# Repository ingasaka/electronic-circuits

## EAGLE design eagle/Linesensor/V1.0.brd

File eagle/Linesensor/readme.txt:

Linesensor V1.0 by ASAKA 2015

Popis:

Maximalne pouzitelne napajacie napatie +5V.

PINY:

1 - OUT 2 - from IC2 
2 - OUT 1 - from IC1
3 - OUT 4 - from IC4
4 - OUT 3 - from IC3
5 - GND
6 - V+(max.+5V)

Video nahlad: https://www.youtube.com/watch?v=R8Qme-guCv8

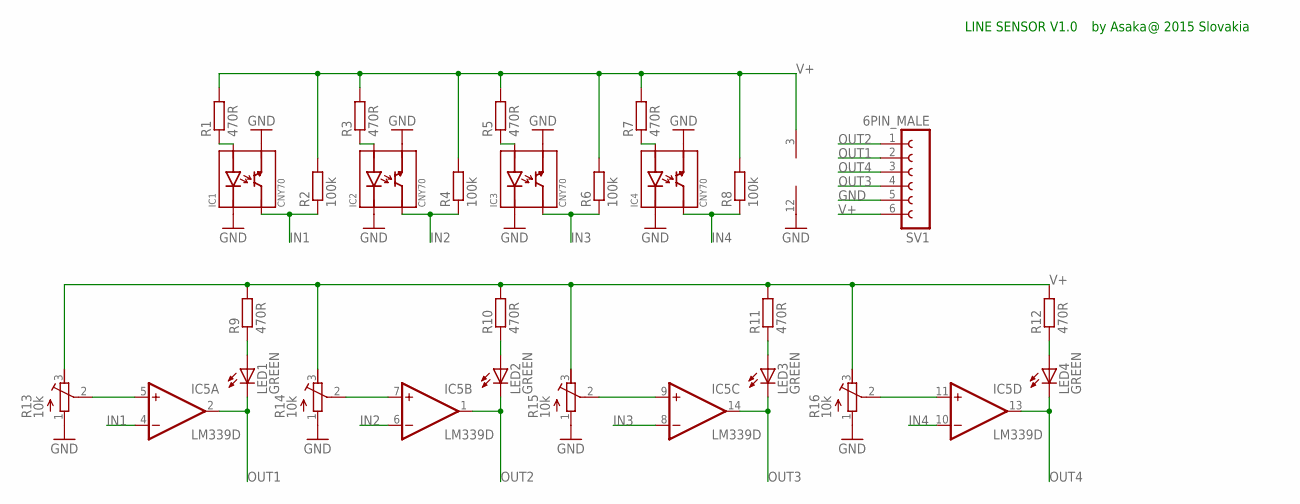
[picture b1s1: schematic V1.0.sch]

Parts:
IC1, IC2, IC3, IC4: CNY70
IC5: LM339D; SO14
LED1, LED2, LED3, LED4: GREEN; CHIP-LED0805
R1, R3, R5, R7, R9, R10, R11, R12: 470R; M0805
R2, R4, R6, R8: 100k; M0805
R13, R14, R15, R16: 10k; RTRIM3202
SV1: 6PIN_MALE; FE06

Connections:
GND: IC1.DE, IC1.EK, IC2.DE, IC2.EK, IC3.DE, IC3.EK, IC4.DE, IC4.EK, IC5.12 (GND), R13.1 (E), R14.1 (E), R15.1 (E), R16.1 (E), SV1.5
IN1: IC1.DC, IC5.4 (-IN), R2.1
IN2: IC2.DC, IC5.6 (-IN), R4.1
IN3: IC3.DC, IC5.8 (-IN), R6.1
IN4: IC4.DC, IC5.10 (-IN), R8.1
unnamed: IC5.5 (+IN), R13.2 (S)
unnamed: IC5.7 (+IN), R14.2 (S)
unnamed: IC5.9 (+IN), R15.2 (S)
unnamed: IC5.11 (+IN), R16.2 (S)
unnamed: LED1.A, R9.1
unnamed: LED2.A, R10.1
unnamed: LED3.A, R11.1
unnamed: LED4.A, R12.1
unnamed: IC1.EA, R1.1
unnamed: IC2.EA, R3.1
unnamed: IC3.EA, R5.1
unnamed: IC4.EA, R7.1
OUT1: IC5.2 (OUT), LED1.C, SV1.2
OUT2: IC5.1 (OUT), LED2.C, SV1.1
OUT3: IC5.14 (OUT), LED3.C, SV1.4
OUT4: IC5.13 (OUT), LED4.C, SV1.3
V+: IC5.3 (V+), R1.2, R2.2, R3.2, R4.2, R5.2, R6.2, R7.2, R8.2, R9.2, R10.2, R11.2, R12.2, R13.3 (A), R14.3 (A), R15.3 (A), R16.3 (A), SV1.6

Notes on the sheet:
LINE SENSOR V1.0
by Asaka
@ 2015 Slovakia

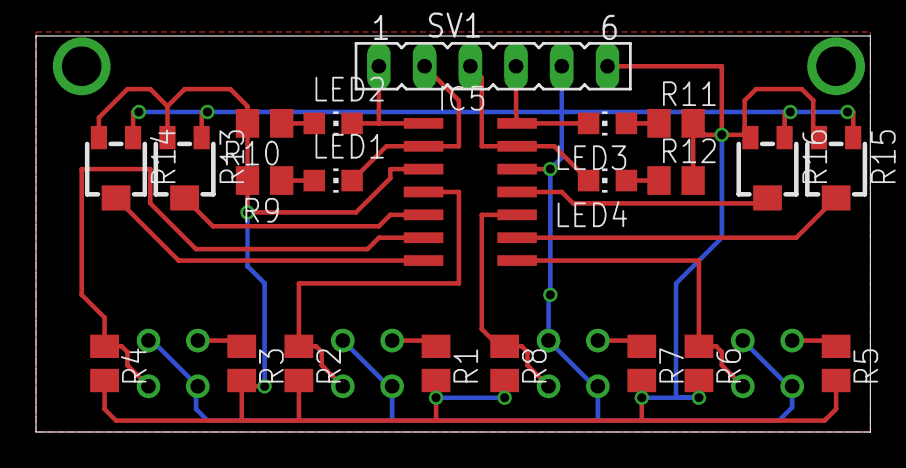
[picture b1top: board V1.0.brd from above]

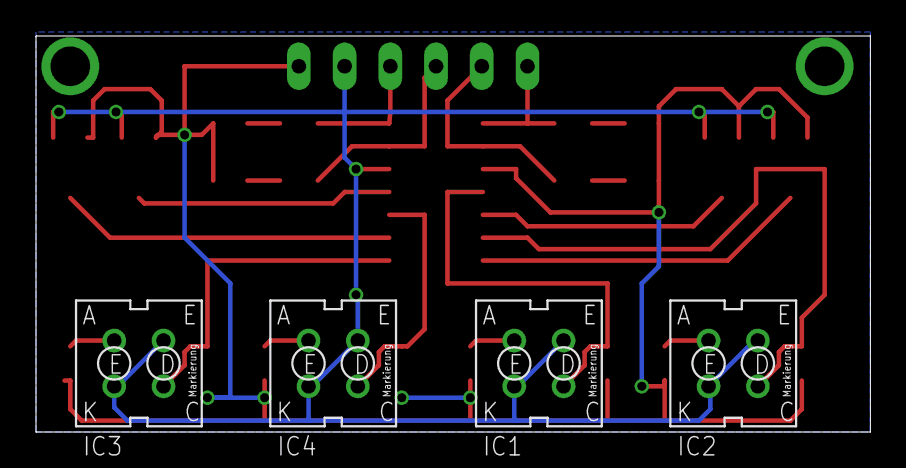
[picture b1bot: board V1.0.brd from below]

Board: 2 copper layers, 46.4 x 22.0 mm, 26 parts (4 on the bottom side), 22 nets.

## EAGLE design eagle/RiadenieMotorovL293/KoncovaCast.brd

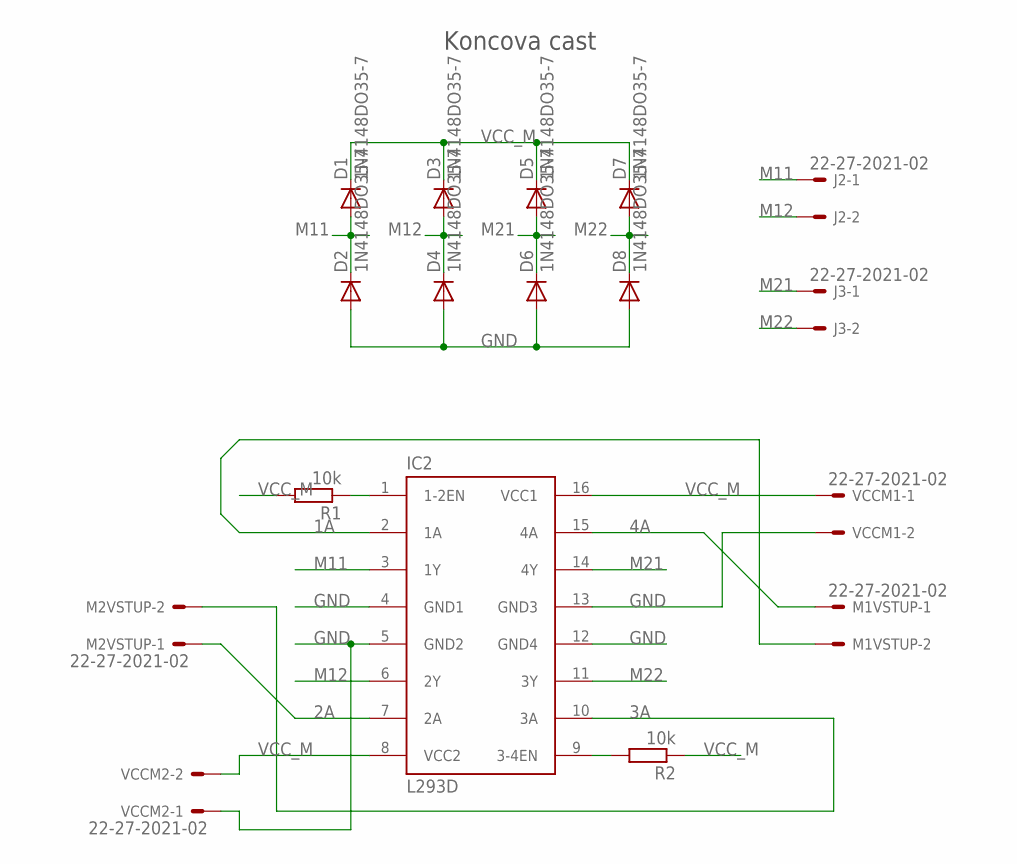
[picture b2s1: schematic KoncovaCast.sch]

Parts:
D1, D2, D3, D4, D5, D6, D7, D8: 1N4148DO35-7; DO35-7
IC2: L293D; DIL16
J2, J3: 22-27-2021-02; 6410-02
M1VSTUP, M2VSTUP: 22-27-2021-02; 6410-02
R1, R2: 10k; 0204V
VCCM1, VCCM2: 22-27-2021-02; 6410-02

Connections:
1A: IC2.2 (1A), M1VSTUP.2
2A: IC2.7 (2A), M2VSTUP.1
3A: IC2.10 (3A), M2VSTUP.2
4A: IC2.15 (4A), M1VSTUP.1
GND: D2.A, D4.A, D6.A, D8.A, IC2.4 (GND1), IC2.5 (GND2), IC2.12 (GND4), IC2.13 (GND3), VCCM1.2, VCCM2.1
M11: D1.A, D2.C, IC2.3 (1Y), J2.1
M12: D3.A, D4.C, IC2.6 (2Y), J2.2
M21: D5.A, D6.C, IC2.14 (4Y), J3.1
M22: D7.A, D8.C, IC2.11 (3Y), J3.2
unnamed: IC2.1 (1-2EN), R1.1
unnamed: IC2.9 (3-4EN), R2.2
VCC_M: D1.C, D3.C, D5.C, D7.C, IC2.8 (VCC2), IC2.16 (VCC1), R1.2, R2.1, VCCM1.1, VCCM2.2

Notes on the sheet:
Koncova cast

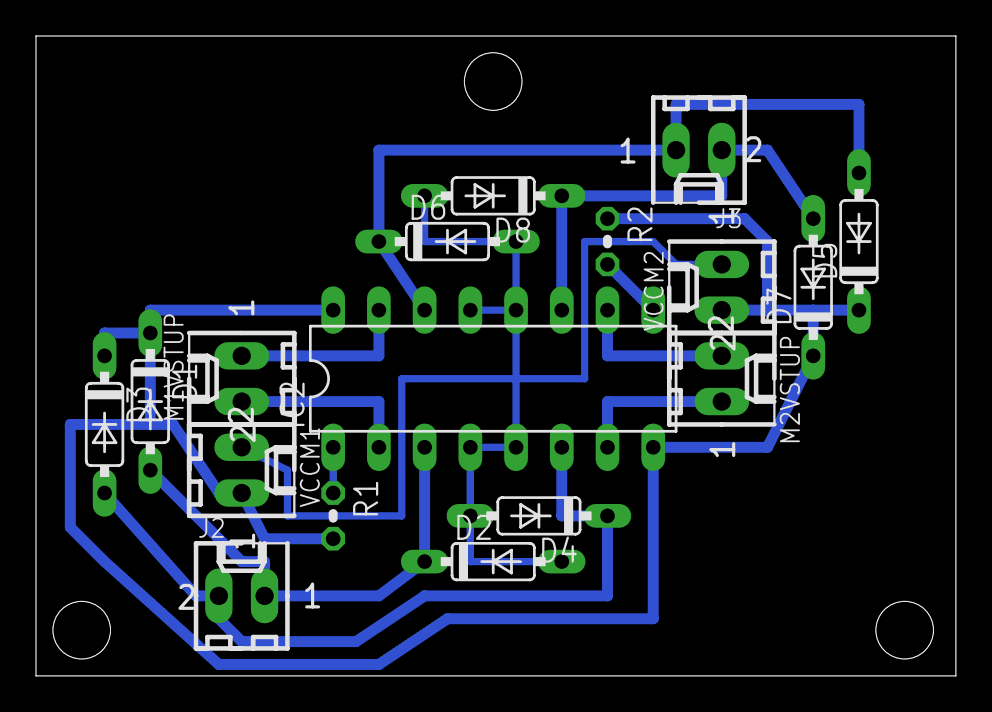
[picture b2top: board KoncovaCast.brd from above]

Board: 2 copper layers, 51.1 x 35.5 mm, 17 parts (0 on the bottom side), 12 nets.

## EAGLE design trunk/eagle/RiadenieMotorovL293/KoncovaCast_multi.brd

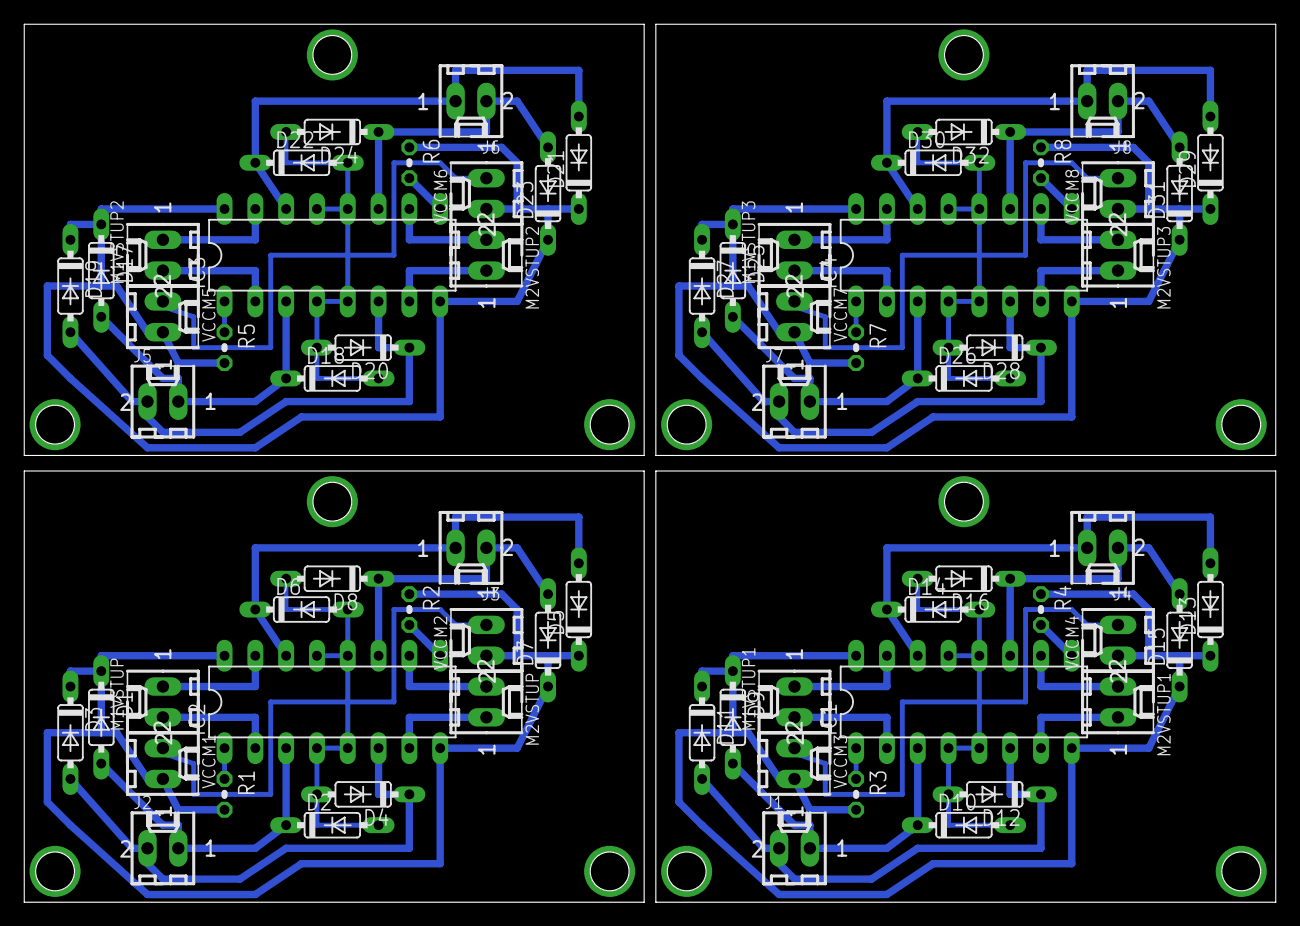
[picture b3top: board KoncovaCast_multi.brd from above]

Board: 2 copper layers, 103.2 x 72.4 mm, 68 parts (0 on the bottom side), 48 nets.

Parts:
D1, D2, D3, D4, D5, D6, D7, D8, D9, D10, D11, D12, D13, D14, D15, D16, D17, D18, D19, D20, D21, D22, D23, D24, D25, D26, D27, D28, D29, D30, D31, D32: 1N4148DO35-7; DO35-7
IC1, IC2, IC3, IC4: L293D; DIL16
J1, J2, J3, J4, J5, J6, J7, J8: 22-27-2021-02; 6410-02
M1VSTUP, M1VSTUP1, M1VSTUP2, M1VSTUP3, M2VSTUP, M2VSTUP1, M2VSTUP2, M2VSTUP3: 22-27-2021-02; 6410-02
R1, R2, R3, R4, R5, R6, R7, R8: 10k; 0204V
VCCM1, VCCM2, VCCM3, VCCM4, VCCM5, VCCM6, VCCM7, VCCM8: 22-27-2021-02; 6410-02

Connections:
1A: IC2.2, M1VSTUP.2
1A1: IC1.2, M1VSTUP1.2
1A2: IC3.2, M1VSTUP2.2
1A3: IC4.2, M1VSTUP3.2
2A: IC2.7, M2VSTUP.1
2A1: IC1.7, M2VSTUP1.1
2A2: IC3.7, M2VSTUP2.1
2A3: IC4.7, M2VSTUP3.1
3A: IC2.10, M2VSTUP.2
3A1: IC1.10, M2VSTUP1.2
3A2: IC3.10, M2VSTUP2.2
3A3: IC4.10, M2VSTUP3.2
4A: IC2.15, M1VSTUP.1
4A1: IC1.15, M1VSTUP1.1
4A2: IC3.15, M1VSTUP2.1
4A3: IC4.15, M1VSTUP3.1
GND: D2.A, D4.A, D6.A, D8.A, IC2.4, IC2.5, IC2.12, IC2.13, VCCM1.2, VCCM2.1
GND1: D10.A, D12.A, D14.A, D16.A, IC1.4, IC1.5, IC1.12, IC1.13, VCCM3.2, VCCM4.1
GND2: D18.A, D20.A, D22.A, D24.A, IC3.4, IC3.5, IC3.12, IC3.13, VCCM5.2, VCCM6.1
GND3: D26.A, D28.A, D30.A, D32.A, IC4.4, IC4.5, IC4.12, IC4.13, VCCM7.2, VCCM8.1
M1: D9.A, D10.C, IC1.3, J1.1
M2: D11.A, D12.C, IC1.6, J1.2
M3: D15.A, D16.C, IC1.11, J4.2
M4: D13.A, D14.C, IC1.14, J4.1
M5: D17.A, D18.C, IC3.3, J5.1
M6: D19.A, D20.C, IC3.6, J5.2
M7: D23.A, D24.C, IC3.11, J6.2
M8: D21.A, D22.C, IC3.14, J6.1
M9: D25.A, D26.C, IC4.3, J7.1
M10: D27.A, D28.C, IC4.6, J7.2
M11: D1.A, D2.C, IC2.3, J2.1
M12: D3.A, D4.C, IC2.6, J2.2
M13: D31.A, D32.C, IC4.11, J8.2
M14: D29.A, D30.C, IC4.14, J8.1
M21: D5.A, D6.C, IC2.14, J3.1
M22: D7.A, D8.C, IC2.11, J3.2
unnamed: IC2.1, R1.1
unnamed: IC2.9, R2.2
unnamed: IC1.1, R3.1
unnamed: IC1.9, R4.2
unnamed: IC3.1, R5.1
unnamed: IC3.9, R6.2
unnamed: IC4.1, R7.1
unnamed: IC4.9, R8.2
VCC_M: D1.C, D3.C, D5.C, D7.C, IC2.8, IC2.16, R1.2, R2.1, VCCM1.1, VCCM2.2
VCC_M1: D9.C, D11.C, D13.C, D15.C, IC1.8, IC1.16, R3.2, R4.1, VCCM3.1, VCCM4.2
VCC_M2: D17.C, D19.C, D21.C, D23.C, IC3.8, IC3.16, R5.2, R6.1, VCCM5.1, VCCM6.2
VCC_M3: D25.C, D27.C, D29.C, D31.C, IC4.8, IC4.16, R7.2, R8.1, VCCM7.1, VCCM8.2

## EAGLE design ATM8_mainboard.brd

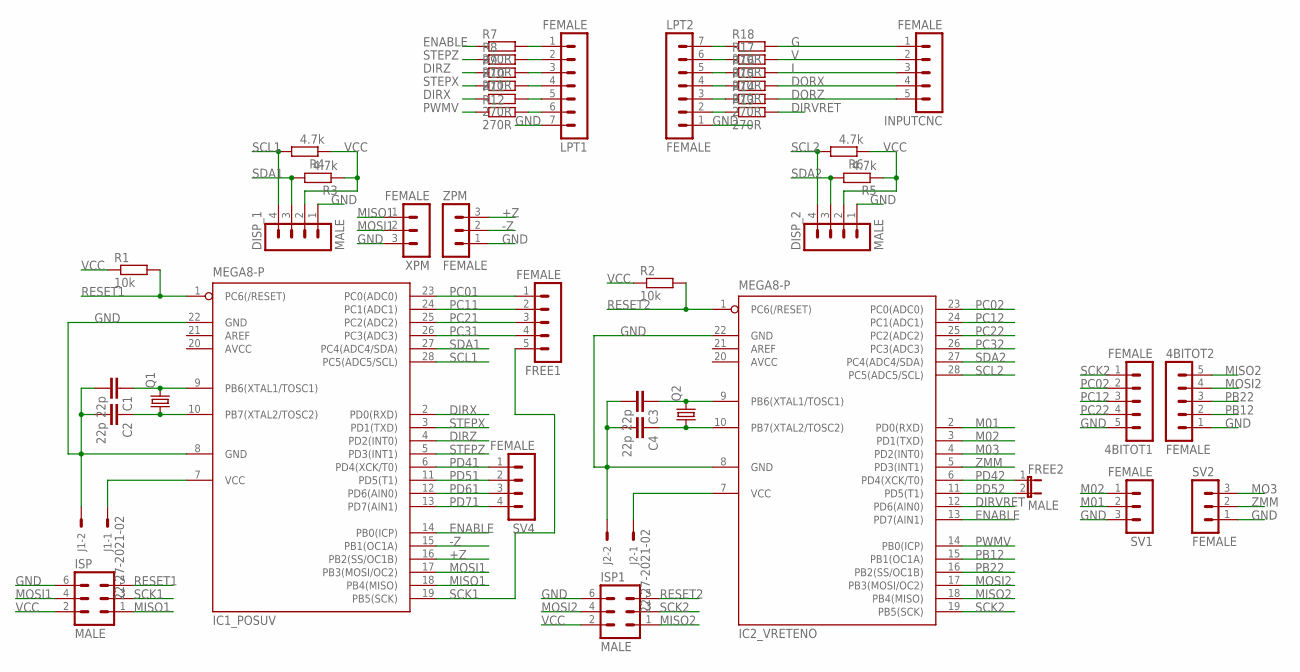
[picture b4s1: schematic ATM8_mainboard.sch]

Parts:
4BITOT1, 4BITOT2: FEMALE; MA05-1
C1, C2, C3, C4: 22p; C025-024X044
DISP_1, DISP_2: MALE; MA04-1
FREE1: FEMALE; MA05-1
FREE2: MALE; JP1
IC1_POSUV, IC2_VRETENO: MEGA8-P; DIL28-3
INPUTCNC: FEMALE; MA05-1
ISP, ISP1: MALE; MA03-2
J1, J2: 22-27-2021-02; 6410-02
LPT1, LPT2: FEMALE; MA07-1
Q1, Q2: CRYSTALHC49S; HC49/S
R1, R2: 10k; 0207/7
R3, R4, R5, R6: 4.7k; 0207/10
R7, R8, R9, R11, R12, R13, R14, R15, R16, R17, R18: 270R; 0207/10
R10: R-EU_0207/10; 0207/10
SV1, SV2: FEMALE; MA03-1
SV4: FEMALE; MA04-1
XPM: FEMALE; MA03-1
ZPM: FEMALE; MA03-1

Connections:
+Z: IC1_POSUV.16 (PB2(SS/OC1B)), ZPM.3
-Z: IC1_POSUV.15 (PB1(OC1A)), ZPM.2
AVCC: IC1_POSUV.20 (AVCC), IC2_VRETENO.20 (AVCC)
DIRVRET: IC2_VRETENO.12 (PD6(AIN0)), R13.2
DIRX: IC1_POSUV.2 (PD0(RXD)), R11.1
DIRZ: IC1_POSUV.4 (PD2(INT0)), R9.1
DORX: INPUTCNC.4, R15.2
DORZ: INPUTCNC.5, R14.2
ENABLE: IC1_POSUV.14 (PB0(ICP)), IC2_VRETENO.13 (PD7(AIN1)), R7.1
G: INPUTCNC.1, R18.2
GND: 4BITOT1.5, 4BITOT2.1, C1.2, C2.2, C3.2, C4.2, DISP_1.1, DISP_2.1, IC1_POSUV.8 (GND), IC1_POSUV.22 (GND), IC2_VRETENO.8 (GND), IC2_VRETENO.22 (GND), ISP.6, ISP1.6, J1.2, J2.2, LPT1.7, LPT2.1, SV1.3, SV2.1, XPM.3, ZPM.1
I: INPUTCNC.3, R16.2
M01: IC2_VRETENO.2 (PD0(RXD)), SV1.2
M02: IC2_VRETENO.3 (PD1(TXD)), SV1.1
M03: IC2_VRETENO.4 (PD2(INT0))
MISO1: IC1_POSUV.18 (PB4(MISO)), ISP.1, XPM.1
MISO2: 4BITOT2.5, IC2_VRETENO.18 (PB4(MISO)), ISP1.1
MO3: SV2.3
MOSI1: IC1_POSUV.17 (PB3(MOSI/OC2)), ISP.4, XPM.2
MOSI2: 4BITOT2.4, IC2_VRETENO.17 (PB3(MOSI/OC2)), ISP1.4
unnamed: LPT1.6, R12.2
unnamed: LPT1.5, R11.2
unnamed: LPT1.4, R10.2
unnamed: LPT1.3, R9.2
unnamed: LPT1.2, R8.2
unnamed: LPT1.1, R7.2
unnamed: LPT2.7, R18.1
unnamed: LPT2.6, R17.1
unnamed: LPT2.5, R16.1
unnamed: LPT2.4, R15.1
unnamed: LPT2.3, R14.1
unnamed: LPT2.2, R13.1
PB3: C3.1, IC2_VRETENO.9 (PB6(XTAL1/TOSC1)), Q2.2
PB4: C4.1, IC2_VRETENO.10 (PB7(XTAL2/TOSC2)), Q2.1
PB6: C1.1, IC1_POSUV.9 (PB6(XTAL1/TOSC1)), Q1.2
PB7: C2.1, IC1_POSUV.10 (PB7(XTAL2/TOSC2)), Q1.1
PB12: 4BITOT2.2, IC2_VRETENO.15 (PB1(OC1A))
PB22: 4BITOT2.3, IC2_VRETENO.16 (PB2(SS/OC1B))
PC01: FREE1.1, IC1_POSUV.23 (PC0(ADC0))
PC02: 4BITOT1.2, IC2_VRETENO.23 (PC0(ADC0))
PC11: FREE1.2, IC1_POSUV.24 (PC1(ADC1))
PC12: 4BITOT1.3, IC2_VRETENO.24 (PC1(ADC1))
PC21: FREE1.3, IC1_POSUV.25 (PC2(ADC2))
PC22: 4BITOT1.4, IC2_VRETENO.25 (PC2(ADC2))
PC31: FREE1.4, IC1_POSUV.26 (PC3(ADC3))
PC32: IC2_VRETENO.26 (PC3(ADC3))
PD41: IC1_POSUV.6 (PD4(XCK/T0)), SV4.1
PD42: FREE2.1, IC2_VRETENO.6 (PD4(XCK/T0))
PD51: IC1_POSUV.11 (PD5(T1)), SV4.2
PD52: FREE2.2, IC2_VRETENO.11 (PD5(T1))
PD61: IC1_POSUV.12 (PD6(AIN0)), SV4.3
PD71: IC1_POSUV.13 (PD7(AIN1)), SV4.4
PWMV: IC2_VRETENO.14 (PB0(ICP)), R12.1
RESET1: IC1_POSUV.1 (PC6(/RESET)), ISP.5, R1.2
RESET2: IC2_VRETENO.1 (PC6(/RESET)), ISP1.5, R2.2
SCK1: FREE1.5, IC1_POSUV.19 (PB5(SCK)), ISP.3
SCK2: 4BITOT1.1, IC2_VRETENO.19 (PB5(SCK)), ISP1.3
SCL1: DISP_1.4, IC1_POSUV.28 (PC5(ADC5/SCL)), R4.2
SCL2: DISP_2.4, IC2_VRETENO.28 (PC5(ADC5/SCL)), R6.2
SDA1: DISP_1.3, IC1_POSUV.27 (PC4(ADC4/SDA)), R3.2
SDA2: DISP_2.3, IC2_VRETENO.27 (PC4(ADC4/SDA)), R5.2
STEPX: IC1_POSUV.3 (PD1(TXD)), R10.1
STEPZ: IC1_POSUV.5 (PD3(INT1)), R8.1
V: INPUTCNC.2, R17.2
VCC: DISP_1.2, DISP_2.2, IC1_POSUV.7 (VCC), IC2_VRETENO.7 (VCC), ISP.2, ISP1.2, J1.1, J2.1, R1.1, R2.1, R3.1, R4.1, R5.1, R6.1
ZMM: IC2_VRETENO.5 (PD3(INT1)), SV2.2

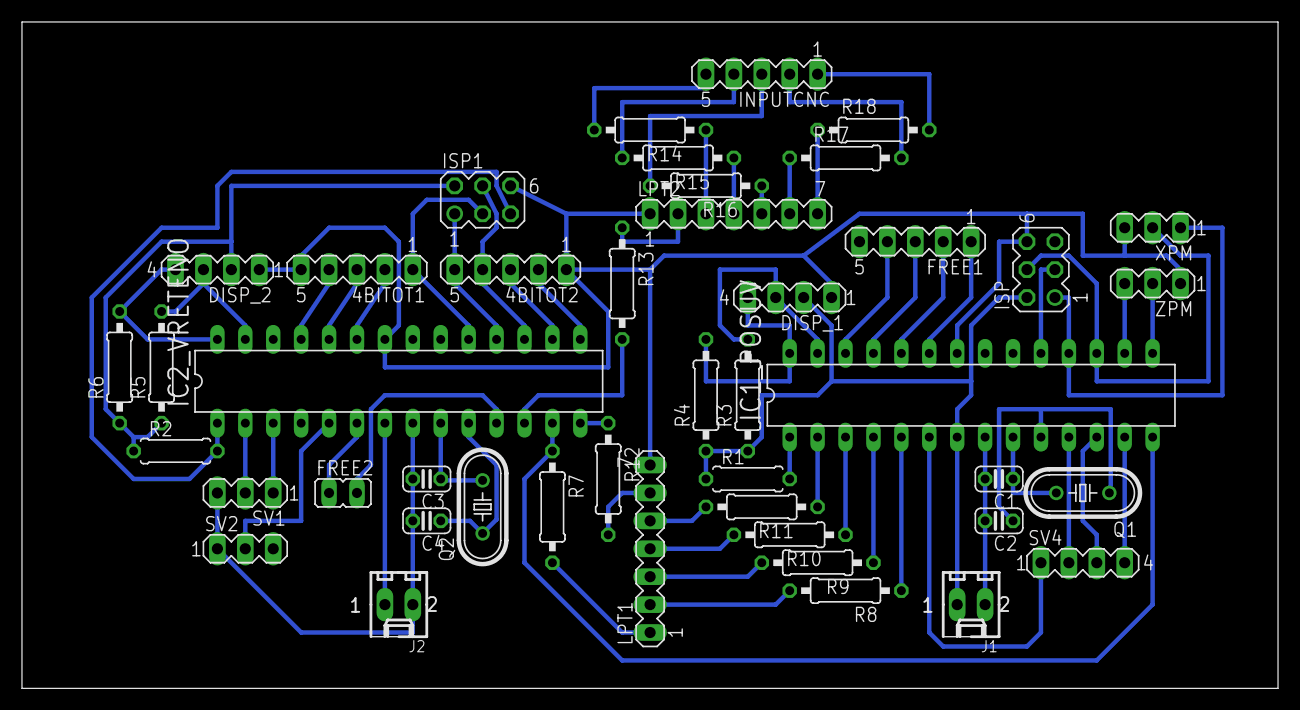
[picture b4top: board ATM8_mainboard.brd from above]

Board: 2 copper layers, 114.3 x 60.6 mm, 44 parts (0 on the bottom side), 63 nets.

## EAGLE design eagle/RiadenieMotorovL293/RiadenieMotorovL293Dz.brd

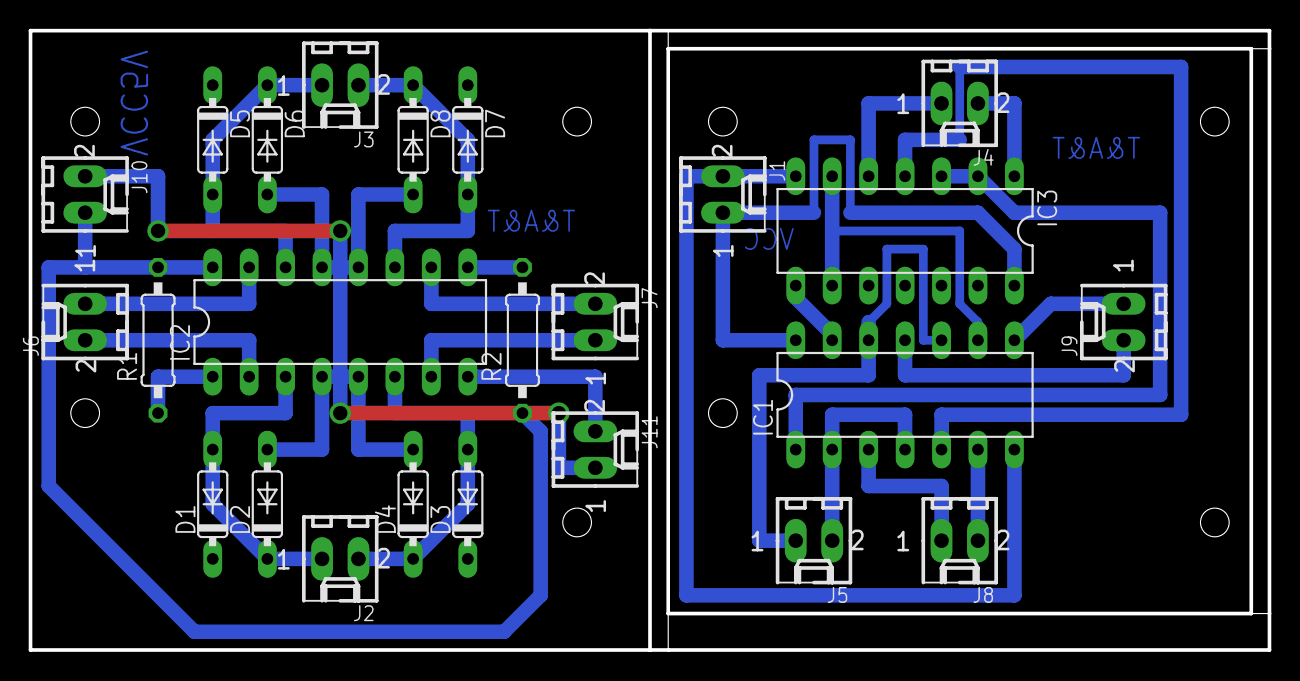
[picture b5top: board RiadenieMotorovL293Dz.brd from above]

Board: 2 copper layers, 86.4 x 43.2 mm, 24 parts (0 on the bottom side), 27 nets.

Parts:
D1, D2, D3, D4, D5, D6, D7, D8: 1N4148DO35-7; DO35-7
IC1: 74AC08N; DIL14
IC2: L293D; DIL16
IC3: 74AC04N; DIL14
J1, J2, J3, J4, J5, J6, J7, J8, J9, J10, J11: 22-27-2021-02; 6410-02
R1, R2: 10k; 0207/10

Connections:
1A: IC2.2, J6.2
1A1: IC1.3, J8.1
2A: IC2.7, J7.1
2A1: IC1.6, J8.2
3A: IC2.10, J7.2
3A1: IC1.8, J9.1
4A: IC2.15, J6.1
4A1: IC1.11, J9.2
GND1: IC1.7, IC3.7, J1.2
GND2: D2.A, D4.A, D6.A, D8.A, IC2.4, IC2.5, IC2.12, IC2.13, J10.2, J11.1
M1: IC3.1, J4.2
M2: IC3.5, J4.1
M11: D1.A, D2.C, IC2.3, J2.1
M12: D3.A, D4.C, IC2.6, J2.2
M21: D5.A, D6.C, IC2.14, J3.1
M22: D7.A, D8.C, IC2.11, J3.2
unnamed: IC2.1, R1.1
unnamed: IC2.9, R2.2
PWM_M1: IC1.2, IC1.4, J5.2
PWM_M2: IC1.10, IC1.12, J5.1
ULEFT1: IC1.1, IC3.2, IC3.3
ULEFT2: IC1.9, IC3.6, IC3.9
URIGHT1: IC1.5, IC3.4
URIGHT2: IC1.13, IC3.8
VCC1: IC1.14, IC3.14, J1.1
VCC2: IC2.8, IC2.16, J10.1, J11.2, R1.2, R2.1
VCC_M: D1.C, D3.C, D5.C, D7.C

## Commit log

2013-06-06 Initial directory structure.
2013-06-06 Posledne upravy v dokumente. Nejasne su Dorazy a GVI ci maju byt pripojene na mikrocip alebo priamo len na LPT????
2013-06-06 Uprava... Pribudlo M01,M02,M03 ale ZMM neviem kam pripojit. Na to sa zabudlo... Predosle problemy pretrvavaju....
2013-07-05 Adresar pre projekty z EAGLE
2015-12-15 Migrating wiki contents from Google Code
2015-12-20 Linesensor
    Linesensor for robotics V1.0
2016-01-14 Mala uprava
    Pridal nahladove foto a upravil readme file.
